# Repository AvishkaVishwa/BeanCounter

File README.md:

# 🛠 BeanCounter – SMT Parts Counting Tool (Forked)

This is a **fork of the original BeanCounter project** by Nick Poole. The **BeanCounter** is a compact SMT parts counting tool designed to accurately track electronic components in carrier tapes. It is powered by an **ATtiny861V-10MU microcontroller** and features an **IR sensor-based counting system** with a **7-segment display**.

---

## 🚀 Features
✅ Counts SMT parts in carrier tapes efficiently  
✅ Supports **Inventory Mode** (fast, no direction tracking) and **Dispense Mode** (precise, directional counting)  
✅ **7-segment LED display** for real-time count tracking  
✅ **EEPROM storage** for user settings (tape pitch, mode selection)  
✅ **Self-test function** for IR sensor diagnostics  
✅ Optimized firmware written in **Arduino (C++)** using **Spence Konde's ATTinyCore**  

---

## 🔧 Enhancements in This Fork
🚀 Improved firmware with optimized **state management**  
🚀 Fixed pin definitions and **hardware configurations**  
🚀 Enhanced **timer settings and IR sensor handling**  
🚀 Refined **power efficiency and EEPROM usage**  

---

## 📂 Getting Started
### 🖥️ Clone the Repository
```sh
git clone https://github.com/YourGitHubUsername/BeanCounter.git
cd BeanCounter
```

## Flash the ATtiny861 Using AVRDude
```sh   
avrdude -c usbasp -p t861 -U flash:w:BeanCounter_V10.ino.hex:i
```

## 🛠️ Modify and Customize

Open the project in Arduino IDE
Install Spence Konde's ATTinyCore for ATtiny861V-10MU
Adjust settings (tape pitch, counting mode, etc.) in EEPROM

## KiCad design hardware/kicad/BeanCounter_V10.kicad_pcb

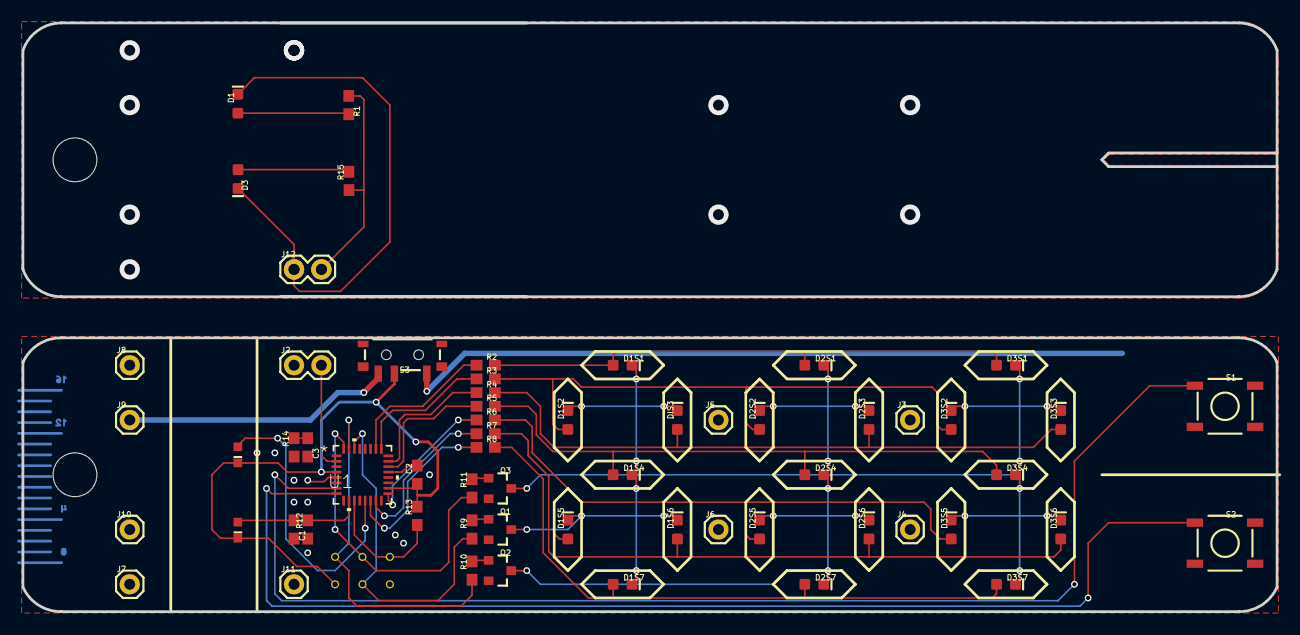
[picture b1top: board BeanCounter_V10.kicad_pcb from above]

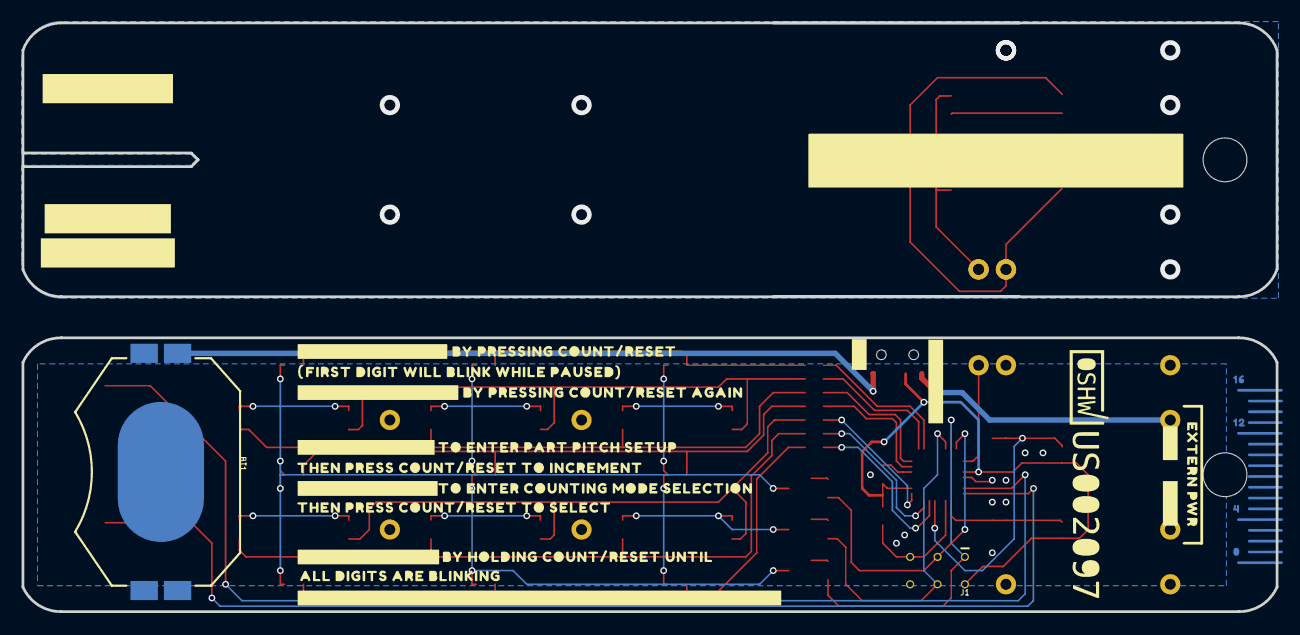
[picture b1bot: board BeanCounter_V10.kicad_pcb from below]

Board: 2 copper layers, 116.3 x 54.6 mm, 95 parts (32 on the bottom side), 37 nets.

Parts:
@HOLE0, @HOLE1: (no value)
BT1: BATTCON_20MM_4LEGS_OVERPASTE_INNER
C1, C2, C3: 0.1uF; 0603
D1, D3: IR LED; LED-0603
D1S1, D1S2, D1S4, D1S5, D1S6, D1S7, D2S1, D2S2, D2S3, D2S4, D2S5, D2S6, D2S7, D3S1, D3S2, D3S3, D3S4, D3S5, D3S6, D3S7: LED-0603
DIS3: LED-0603
J1: AVR_SPI_PROG_3X2TESTPOINTS; 2X3_TEST_POINTS
J2, J12: 1X02
J3, J4, J5, J6, J7, J8, J9, J10, J11: 1X01
Q1, Q2, Q3: 220mA/50V/3.5Ω; SOT23-3
R1, R9, R10, R11, R12, R13, R14, R15: 1k; 0603
R2, R3, R4, R5, R6, R7, R8: 33; 0603
S1, S2: MOMENTARY-SWITCH-SPST-SMD-5.2MM-TALL; TACTILE_SWITCH_SMD_5.2MM
S3: SWITCH_SPST_SMD_A
U1: ATTINY861V-10MU; 32M1-A_ATM
U$1: OSHWBC#SVG0
U$2: EXTERN_PWR0
U$3: #PAUSE_COUNTING#0
U$4: #PRESS_SETUP_X1#0
U$5: 00
U$6: #_3V#0
U$7: #_GND#0
U$8: THEN_PRESS_COUNT#RESET_TO_INCREMENT0
U$9: BY_PRESSING_COUNT#RESET0
U$10: FIRST_DIGIT_WILL_BLINK_WHILE_PAUSED#_0
U$11: #_0
U$12: #RESUME_COUNTING#0
U$13: BY_PRESSING_COUNT#RESET_AGAIN0
U$14: TO_ENTER_PART_PITCH_SETUP0
U$15: #PRESS_SETUP_X2#0
U$16: TO_ENTER_COUNTING_MODE_SELECTION0
U$17: THEN_PRESS_COUNT#RESET_TO_SELECT0
U$18: #RESET_COUNTER#0
U$19: BY_HOLDING_COUNT#RESET_UNTIL0
U$20: 40
U$21: 120
U$22: 160
U$23: #ON#0
U$24: #OFF#EXT#0
U$25: ALL_DIGITS_ARE_BLINKING0
U$26: #COMPLETE_DOCS_AT_GITHUB#COM#NPOOLE#BEANCOUNTER#0
U$27: #COUNT#0
U$28: #RESET#0
U$29: #SETUP#0
U$30: LOGO#SVG0
U$31, U$32: B19H1PT; HARVATEK_DETECTOR

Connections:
0: R2.1, U1.26
1: R3.1, U1.25
2: R4.1, U1.23
3: R5.1, U1.22
4: R6.1, U1.17
5: R7.1, U1.15
6: R8.1, U1.14
8/COPI: J1.4, R9.1, U1.30
9/CIPO: J1.1, R10.1, U1.31
10/SCK: J1.3, R11.1, U1.32
11: J2.2, U1.2
12: S1.1, U1.7
13: S2.1, U1.8
GND: BT1.2, C1.2, C2.2, C3.2, J1.6, J2.1, J10.1, Q1.2, Q2.2, Q3.2, R12.1, R14.1, S1.3, S2.3, U1.5, U1.21
IR_DETECTOR_A: C1.1, R12.2, U1.10, U$31.P$2
IR_DETECTOR_B: C3.1, R14.2, U1.13, U$32.P$2
unnamed: BT1.1, S3.3
unnamed: D1S1.C, D1S2.C, D1S4.C, D1S5.C, D1S6.C, D1S7.C, DIS3.C, Q1.3
unnamed: Q2.1, R10.2
unnamed: Q1.1, R9.2
unnamed: D2S1.C, D2S2.C, D2S3.C, D2S4.C, D2S5.C, D2S6.C, D2S7.C, Q2.3
unnamed: Q3.1, R11.2
unnamed: D3S1.C, D3S2.C, D3S3.C, D3S4.C, D3S5.C, D3S6.C, D3S7.C, Q3.3
unnamed: J12.2, R1.1, R15.1
unnamed: D1.C, D3.C, J12.1
unnamed: D3.A, R15.2
unnamed: D1.A, R1.2
SEG1: D1S1.A, D2S1.A, D3S1.A, R2.2
SEG2: D1S2.A, D2S2.A, D3S2.A, R3.2
SEG3: D2S3.A, D3S3.A, DIS3.A, R4.2
SEG4: D1S4.A, D2S4.A, D3S4.A, R5.2
SEG5: D1S5.A, D2S5.A, D3S5.A, R6.2
SEG6: D1S6.A, D2S6.A, D3S6.A, R7.2
SEG7: D1S7.A, D2S7.A, D3S7.A, R8.2
V_BATT: C2.1, J1.2, R13.2, S3.2, U1.4, U1.18, U$31.P$1, U$32.P$1
V_EXT: J9.1, S3.1
~RESET: J1.5, R13.1, U1.11

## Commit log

2025-02-06 Update README.md to reflect forked status and enhance feature descriptions
2025-02-07 Update README.md to include instructions for flashing the ATtiny861 and customization steps
2025-02-11 Add initial KiCad project files for BeanCounter_V10
